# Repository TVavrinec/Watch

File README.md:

# Watch
ESP32_S3_MINI watch with 12 LED circle, buzzer, one button and lunette.
The watch is designed for a 1200mA Li-Ion battery and has complete battery management.

Fusion model: https://a360.co/3ve1P58

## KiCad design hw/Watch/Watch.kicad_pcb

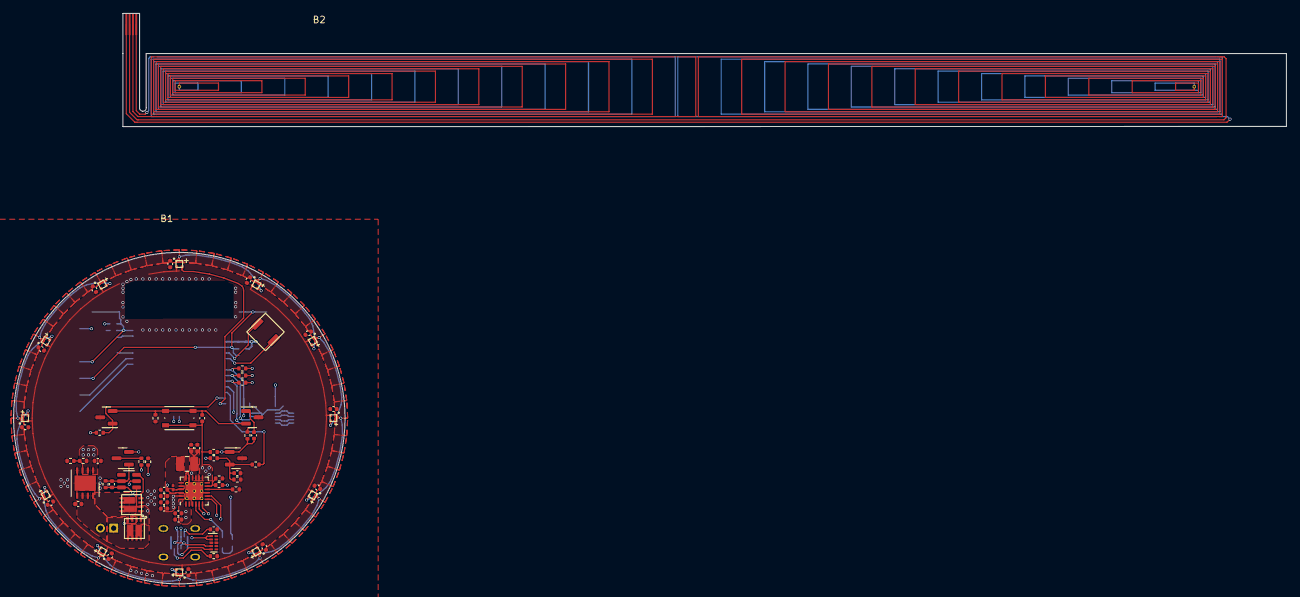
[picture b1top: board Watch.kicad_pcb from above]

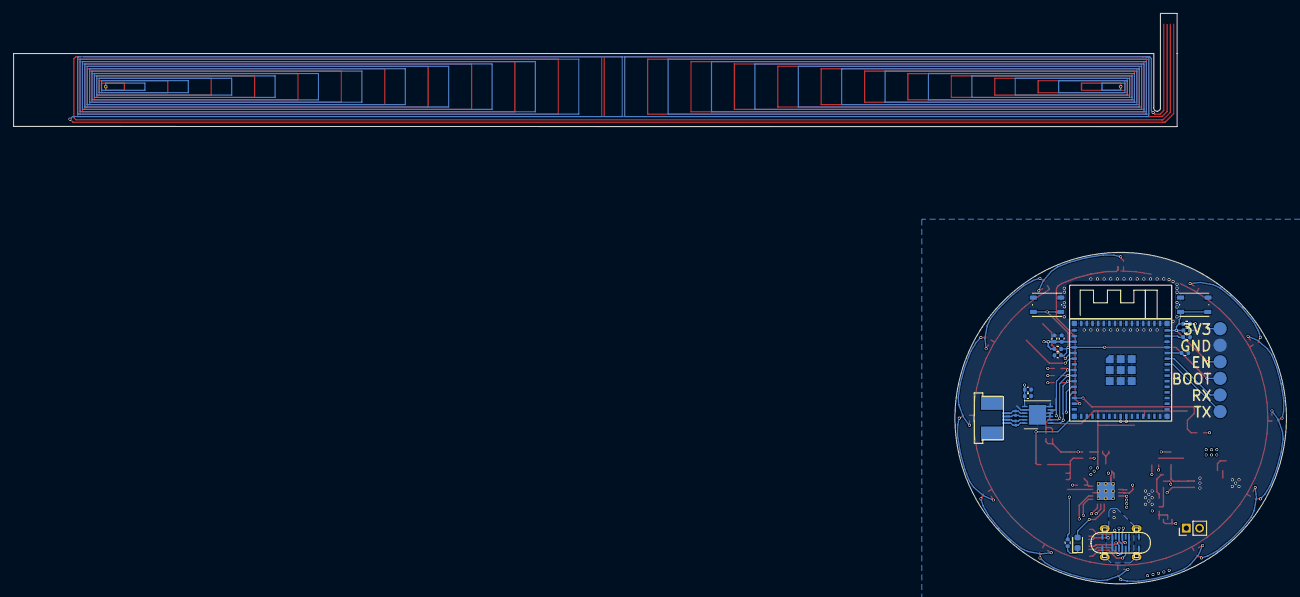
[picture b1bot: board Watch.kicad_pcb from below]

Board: 4 copper layers, 50.0 x 50.0 mm, 99 parts (23 on the bottom side), 64 nets.

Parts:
B1, B2: Board
BZ1: Buzzer; SmallBuzzer
C1, C23, C29, C30, C31, C32, C33: 10u; C_0402_1005Metric
C2, C6, C7, C11, C12, C13, C14, C15, C16, C17, C18, C19, C20, C21, C22: 100n; C_0402_1005Metric
C3, C4, C5, C8, C9, C24, C35: 1u; C_0402_1005Metric
C10, C26, C34: 4.7u; C_0402_1005Metric
C25: 47n; C_0201_0603Metric
C27, C28: 1000p; C_0201_0603Metric
D1, D2, D3, D4, D5, D6, D7, D8, D9, D10, D11, D12: WS2812B; WS2812-1010
D14: red; LED_0603_1608Metric
J1: ESP-Programing_conector
J2: Conn_01x02; PinHeader_1x02_P2.00mm_Vertical
J3: Conn_01x04; FFC-FPC_1x04_0.5mm
J7: USB_C_Receptacle_USB2.0; USB-C_vertical
J8: Conn_01x04; FFC-FPC_1x04_0.5mm_cable
L1, L2: L; PCB_coil_linear_N24
L3: 2.2u; L_1008_2520Metric
Q1: Q_PMOS_DGS-L; SOT-23
Q2, Q7: PMOS-2x_BSS84DW; DFN3030
Q3, Q5, Q6: Q_NMOS_DGS-L; SOT-23
R1, R2, R3, R5, R6, R7, R8, R9, R16, R17, R22, R25, R26: 10k; R_0402_1005Metric
R4: 56k; R_0402_1005Metric
R10, R15: 200k; R_0402_1005Metric
R11: 470; R_0402_1005Metric
R12, R24: 5.1k; R_0402_1005Metric
R13, R19: 1M; R_0402_1005Metric
R14, R21: 2k; R_0402_1005Metric
R18: 200; R_0402_1005Metric
R23: 100; R_0402_1005Metric
SW2: EN; SW_Push_1P1T_NO_Vertical_Wuerth_434133025816
SW3: BOOT; SW_Push_1P1T_NO_Vertical_Wuerth_434133025816
SW4: ON; SW_Push_1P1T_NO_Vertical_Wuerth_434133025816
U1: ESP32-S3-MINI
U2: SL8261D-G3JE; SOT-23-6
U3: LDC1x12; WSON-12-1EP_4x4mm_P0.5mm_EP2.6x3mm
U4: LD39200; DFN-8-1EP_4x4mm_P0.8mm_EP2.3x3.24mm
U8: BQ25895RTW; Texas_S-PWQFN-N24_EP2.7x2.7mm_ThermalVias
U9: TPD4E02B04DQA; USON-10_2.5x1.0mm_P0.5mm

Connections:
/L1A: J8.1, L1.2
/L1B: J8.2, L1.1
/L2A: J8.3, L2.2
/L2B: J8.4, L2.1
/MainBoard/3V3: C1.2, C2.2, C5.1, C6.1, C23.1, J1.1 (VCC), R1.1, R2.1, R3.1, R4.2, R6.1, R7.1, R16.2, R17.2, U1.3 (3V3), U3.7 (VDD), U4.1 (OUT), U4.2 (OUT)
/MainBoard/ESP32-S3-MINI/BOOT: C3.1, J1.4 (BOOT), R7.2, SW3.2, U1.4 (IO00-PU)
/MainBoard/ESP32-S3-MINI/D+: J7.A6 (D+), J7.B6 (D+), U1.24 (IO20-D+), U9.5 (IO4)
/MainBoard/ESP32-S3-MINI/D-: J7.A7 (D-), J7.B7 (D-), U1.23 (IO19-D-), U9.4 (IO3)
/MainBoard/ESP32-S3-MINI/EN: C4.1, J1.3 (EN), R6.2, SW2.2, U1.45 (EN)
/MainBoard/ESP32-S3-MINI/IO01: BZ1.1 (-), U1.5 (IO01)
/MainBoard/ESP32-S3-MINI/IO02: BZ1.2 (+), U1.6 (IO02)
/MainBoard/ESP32-S3-MINI/IO07: U1.11 (IO07), U8.8 (OTG)
/MainBoard/ESP32-S3-MINI/IO08: R18.2, U1.12 (IO08)
/MainBoard/ESP32-S3-MINI/IO09: Q5.1 (D), R16.1, U1.13 (IO09)
/MainBoard/ESP32-S3-MINI/IO10: D1.4 (DIN), U1.14 (IO10)
/MainBoard/ESP32-S3-MINI/RX_ESP: J1.5 (RX), U1.40 (IO44-RX)
/MainBoard/ESP32-S3-MINI/TX_ESP: J1.6 (TX), U1.39 (IO43-TX)
/MainBoard/INT: R1.2, U1.8 (IO04), U3.5 (INTB), U8.7 (INT)
/MainBoard/LC-0A: C27.2, J3.1, U3.9 (IN0A)
/MainBoard/LC-0B: C27.1, J3.2, U3.10 (IN0B)
/MainBoard/LC-1A: C28.2, J3.3, U3.11 (IN1A)
/MainBoard/LC-1B: C28.1, J3.4, U3.12 (IN1B)
/MainBoard/LED-RING/5V: C11.1, C12.1, C13.1, C14.1, C15.1, C16.1, C17.1, C18.1, C19.1, C20.1, C21.1, C22.1, C31.1, C32.1, C33.1, D1.2 (VDD), D2.2 (VDD), D3.2 (VDD), D4.2 (VDD), D5.2 (VDD), D6.2 (VDD), D7.2 (VDD), D8.2 (VDD), D9.2 (VDD), D10.2 (VDD), D11.2 (VDD), D12.2 (VDD), U8.23 (PMID)
/MainBoard/PowerManager/Charger/STAT: D14.2 (A), U8.4 (STAT)
/MainBoard/SCL: R2.2, U1.9 (IO05), U3.2 (SDA), U8.6 (SDA)
/MainBoard/SDA: R3.2, U1.10 (IO06), U3.1 (SCL), U8.5 (SCL)
/MainBoard/USB/USB_CC1: J7.A5 (CC1), R24.1
/MainBoard/USB/USB_CC2: J7.B5 (CC2), R12.1
/MainBoard/USB/VBUS: C24.1, C34.1, J7.A4 (VBUS), J7.A9 (VBUS), J7.B4 (VBUS), J7.B9 (VBUS), U8.1 (VBUS), U9.1 (IO1), U9.2 (IO2)
GND: C1.1, C2.1, C3.2, C4.2, C5.2, C6.2, C9.2, C10.2, C11.2, C12.2, C13.2, C14.2, C15.2, C16.2, C17.2, C18.2, C19.2, C20.2, C21.2, C22.2, C23.2, C24.2, C26.2, C29.2, C30.2, C31.2, C32.2, C33.2, C34.2, D1.3 (VSS), D2.3 (VSS), D3.3 (VSS), D4.3 (VSS), D5.3 (VSS), D6.3 (VSS), D7.3 (VSS), D8.3 (VSS), D9.3 (VSS), D10.3 (VSS), D11.3 (VSS), D12.3 (VSS), J1.2 (GND), J7.A1 (GND), J7.A12 (GND), J7.B1 (GND), J7.B12 (GND), J7.S1 (SHIELD), Q3.3 (S), Q5.3 (S), Q6.3 (S), Q7.S2 (S), R5.1, R8.2, R9.2, R12.2, R14.1, R19.1, R23.2, R24.2, R25.1, R26.2, SW2.1, SW3.1, U1.1 (GND), U1.2 (GND), U1.42 (GND), U1.43 (GND), U1.46 (GND), U1.47 (GND), U1.48 (GND), U1.49 (GND), U1.50 (GND), U1.51 (GND), U1.52 (GND), U1.53 (GND), U1.54 (GND), U1.55 (GND), U1.56 (GND), U1.57 (GND), U1.58 (GND), U1.59 (GND), U1.60 (GND), U1.61 (GND), U1.62 (GND), U1.63 (GND), U1.64 (GND), U1.65 (GND), U3.3 (CLKIN), U3.4 (ADDR), U3.6 (SD), U3.8 (GND), U3.13 (GND), U4.4 (GND), U4.9 (GND), U8.9 (~CE), U8.17 (PGND), U8.18 (PGND), U8.25 (PGND), U9.3 (G), U9.8 (G)
unnamed: C25.1, L3.1, U8.19 (SW), U8.20 (SW)
unnamed: C29.1, C30.1, L3.2, R21.2, U8.15 (SYS), U8.16 (SYS)
unnamed: D1.1 (DOUT), D2.4 (DIN)
unnamed: D2.1 (DOUT), D3.4 (DIN)
unnamed: D3.1 (DOUT), D4.4 (DIN)
unnamed: D4.1 (DOUT), D5.4 (DIN)
unnamed: D5.1 (DOUT), D6.4 (DIN)
unnamed: D6.1 (DOUT), D7.4 (DIN)
unnamed: D7.1 (DOUT), D8.4 (DIN)
unnamed: D8.1 (DOUT), D9.4 (DIN)
unnamed: D9.1 (DOUT), D10.4 (DIN)
unnamed: D10.1 (DOUT), D11.4 (DIN)
unnamed: D11.1 (DOUT), D12.4 (DIN)
unnamed: D14.1 (K), R21.1
unnamed: J2.1, Q2.D1 (D), Q2.D2 (D)
unnamed: C7.1, Q1.1 (D), R13.2, U2.5 (VCC)
unnamed: C8.1, Q1.2 (G), Q6.1 (D), R10.1, R15.1
unnamed: Q1.3 (S), R11.2
unnamed: C7.2, Q2.S1 (S), Q2.S2 (S), Q7.S1 (S), R13.1, U2.6 (GND)
unnamed: C8.2, Q3.1 (D), R15.2
unnamed: C35.2, Q3.2 (G), Q5.2 (G), R25.2, SW4.1
unnamed: C9.1, Q6.2 (G), R17.1, R18.1, R19.2
unnamed: Q7.D1 (D), Q7.D2 (D)
unnamed: Q7.G1 (G), U2.1 (OD)
unnamed: Q7.G2 (G), U2.3 (OC)
unnamed: R9.1, U1.41 (IO45-PD)
unnamed: R8.1, U1.44 (IO46-PD)
unnamed: R14.2, U2.2 (VM)
unnamed: R4.1, R5.2, U4.3 (ADJ/SENSE)
unnamed: C25.2, U8.21 (BTST)
unnamed: R23.1, U8.10 (ILIM)
unnamed: C26.1, R22.2, U8.22 (REGN)
unnamed: R22.1, R26.1, U8.11 (TS)
VCC: C10.1, C35.1, J2.2, Q2.G1 (G), Q2.G2 (G), R10.2, R11.1, SW4.2, U4.6 (EN), U4.7 (VCC), U4.8 (VCC), U8.13 (BAT), U8.14 (BAT)

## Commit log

2024-03-13 The basis of schematic
2024-03-14 PCB v0.0.0
2024-03-15 Shift LDO
2024-03-15 README
2024-03-15 Add link to fusion model
2024-03-15 Shift flex connector
